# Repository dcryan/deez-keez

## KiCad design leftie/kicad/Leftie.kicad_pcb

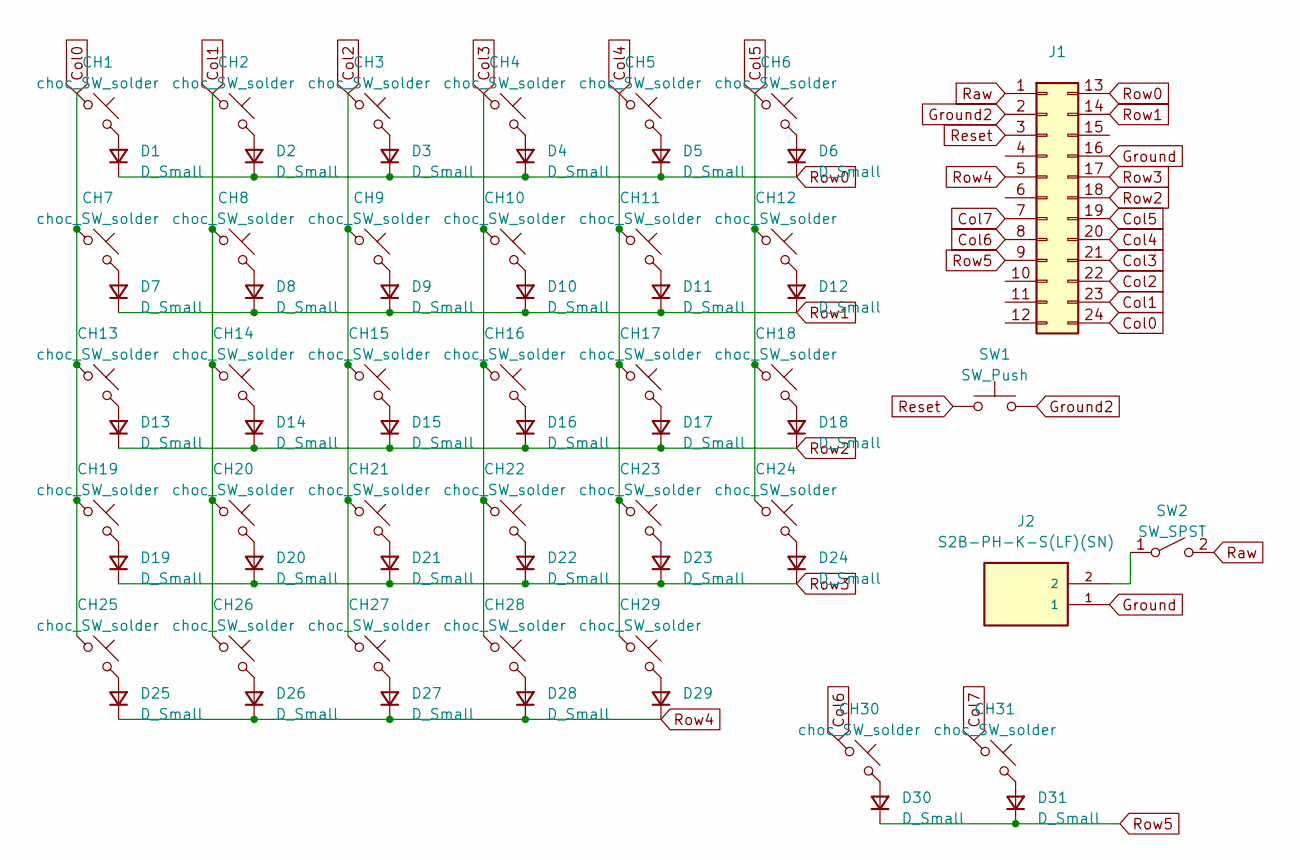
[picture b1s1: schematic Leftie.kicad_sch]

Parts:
CH1, CH2, CH3, CH4, CH5, CH6, CH7, CH8, CH9, CH10, CH11, CH12, CH13, CH14, CH15, CH16, CH17, CH18, CH19, CH20, CH21, CH22, CH23, CH24, CH25, CH26, CH27, CH28, CH29, CH30, CH31: choc_SW_solder; SW_choc_v1_1u
D1, D2, D3, D4, D5, D6, D7, D8, D9, D10, D11, D12, D13, D14, D15, D16, D17, D18, D19, D20, D21, D22, D23, D24, D25, D26, D27, D28, D29, D30, D31: D_Small; D_SOD-123
J1: Conn_02x12_Top_Bottom; ProMicro
J2: S2B-PH-K-S(LF)(SN); JST_S2B-PH-K-S(LF)(SN)
SW1: SW_Push; SW_SKHLLCA010
SW2: SW_SPST; SW_MSK12C02-HB

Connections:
Col0: CH1.1, CH7.1, CH13.1, CH19.1, CH25.1, J1.24
Col1: CH2.1, CH8.1, CH14.1, CH20.1, CH26.1, J1.23
Col2: CH3.1, CH9.1, CH15.1, CH21.1, CH27.1, J1.22
Col3: CH4.1, CH10.1, CH16.1, CH22.1, CH28.1, J1.21
Col4: CH5.1, CH11.1, CH17.1, CH23.1, CH29.1, J1.20
Col5: CH6.1, CH12.1, CH18.1, CH24.1, J1.19
Col6: CH30.1, J1.8
Col7: CH31.1, J1.7
Ground: J1.16, J2.1
Ground2: J1.2, SW1.2
unnamed: CH1.2, D1.2 (A)
unnamed: CH2.2, D2.2 (A)
unnamed: CH3.2, D3.2 (A)
unnamed: CH4.2, D4.2 (A)
unnamed: CH5.2, D5.2 (A)
unnamed: CH6.2, D6.2 (A)
unnamed: CH7.2, D7.2 (A)
unnamed: CH8.2, D8.2 (A)
unnamed: CH9.2, D9.2 (A)
unnamed: CH10.2, D10.2 (A)
unnamed: CH11.2, D11.2 (A)
unnamed: CH12.2, D12.2 (A)
unnamed: CH13.2, D13.2 (A)
unnamed: CH14.2, D14.2 (A)
unnamed: CH15.2, D15.2 (A)
unnamed: CH16.2, D16.2 (A)
unnamed: CH17.2, D17.2 (A)
unnamed: CH18.2, D18.2 (A)
unnamed: CH19.2, D19.2 (A)
unnamed: CH20.2, D20.2 (A)
unnamed: CH21.2, D21.2 (A)
unnamed: CH22.2, D22.2 (A)
unnamed: CH23.2, D23.2 (A)
unnamed: CH24.2, D24.2 (A)
unnamed: CH25.2, D25.2 (A)
unnamed: CH26.2, D26.2 (A)
unnamed: CH27.2, D27.2 (A)
unnamed: CH28.2, D28.2 (A)
unnamed: CH29.2, D29.2 (A)
unnamed: CH30.2, D30.2 (A)
unnamed: CH31.2, D31.2 (A)
unnamed: J2.2, SW2.1 (A)
Raw: J1.1, SW2.2 (B)
Reset: J1.3, SW1.1
Row0: D1.1 (K), D2.1 (K), D3.1 (K), D4.1 (K), D5.1 (K), D6.1 (K), J1.13
Row1: D7.1 (K), D8.1 (K), D9.1 (K), D10.1 (K), D11.1 (K), D12.1 (K), J1.14
Row2: D13.1 (K), D14.1 (K), D15.1 (K), D16.1 (K), D17.1 (K), D18.1 (K), J1.18
Row3: D19.1 (K), D20.1 (K), D21.1 (K), D22.1 (K), D23.1 (K), D24.1 (K), J1.17
Row4: D25.1 (K), D26.1 (K), D27.1 (K), D28.1 (K), D29.1 (K), J1.5
Row5: D30.1 (K), D31.1 (K), J1.9

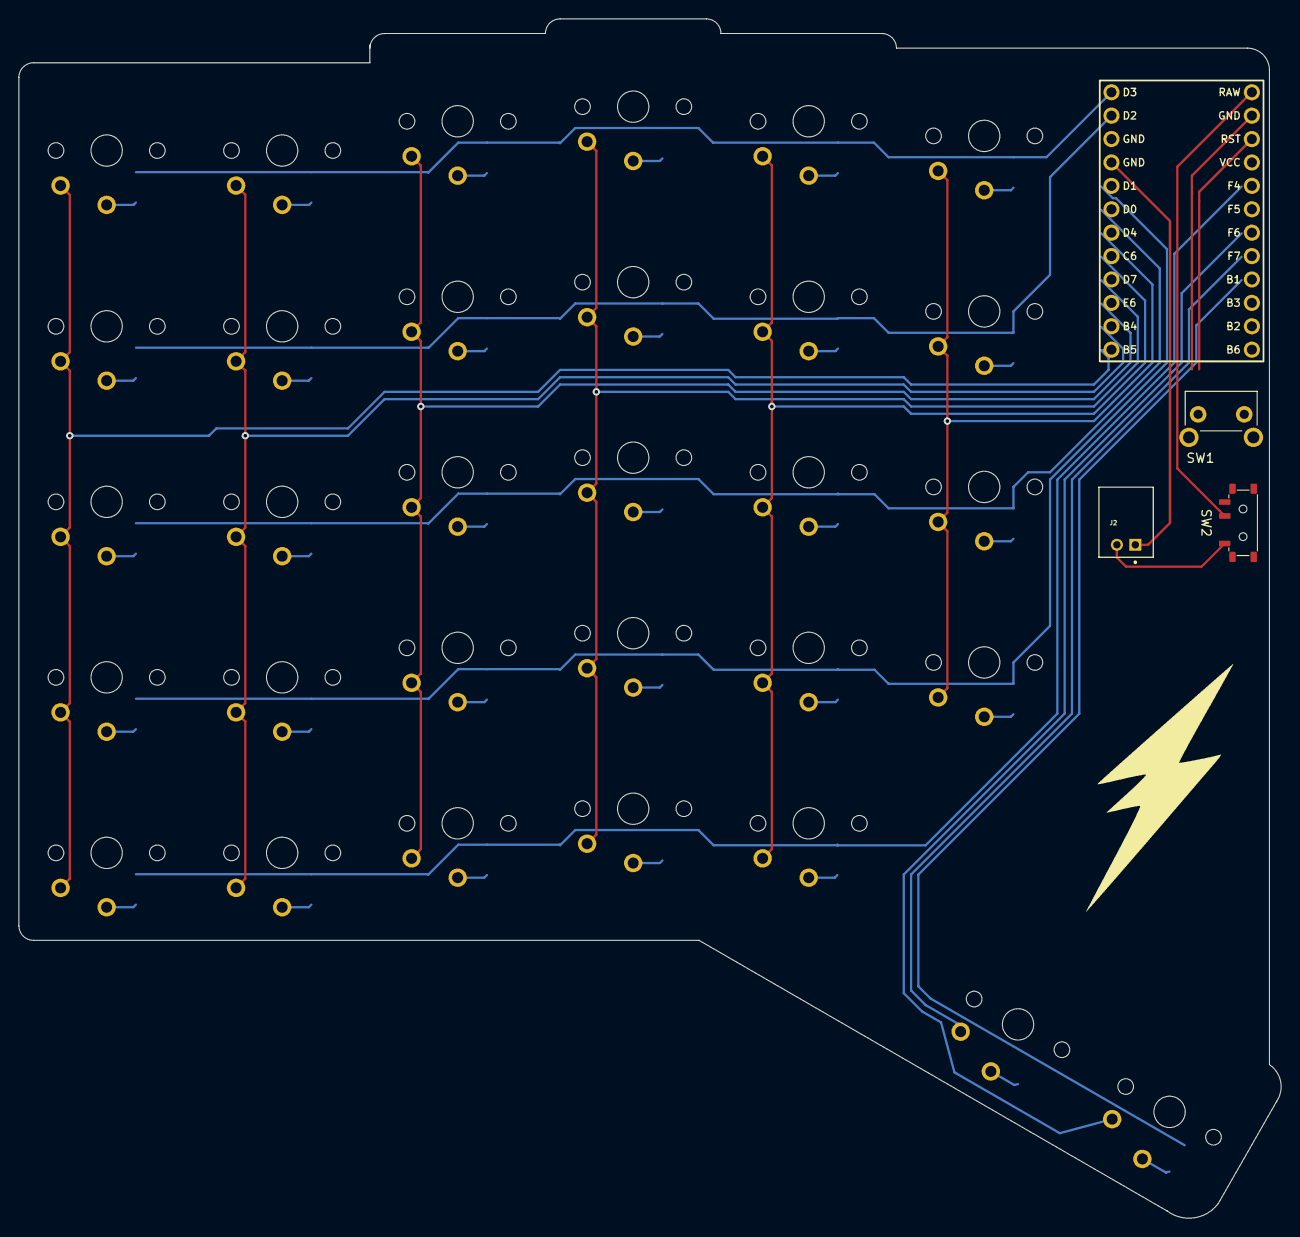
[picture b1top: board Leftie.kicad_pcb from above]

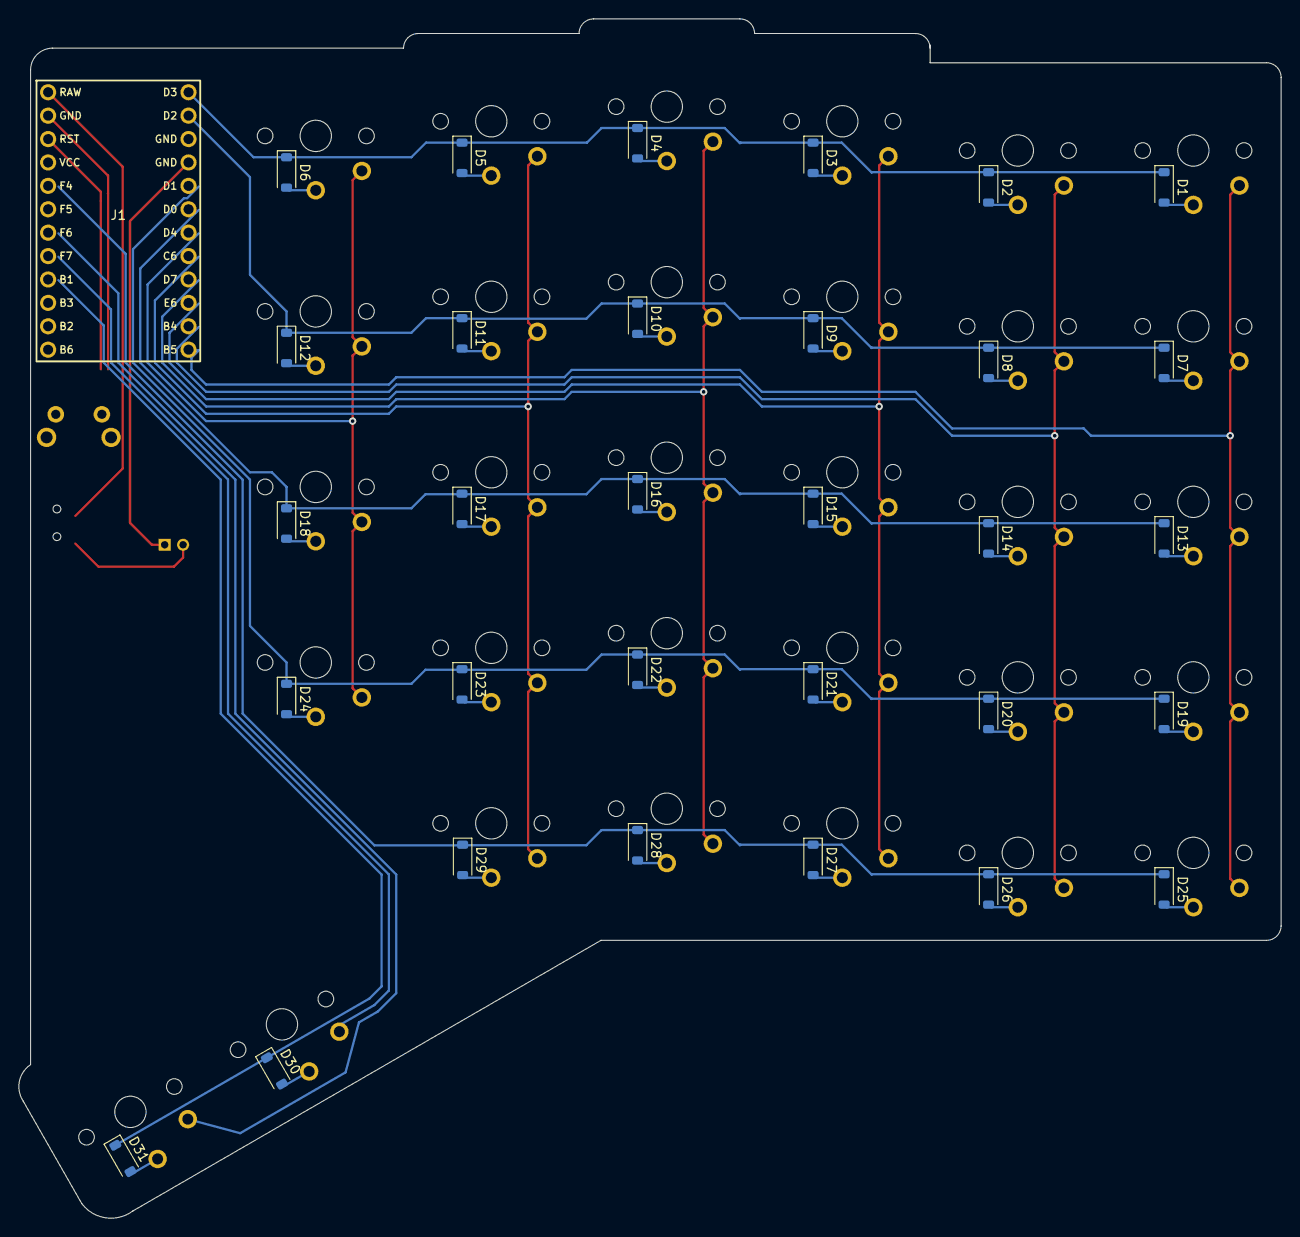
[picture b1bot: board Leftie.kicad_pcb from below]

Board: 2 copper layers, 137.0 x 130.2 mm, 66 parts (32 on the bottom side), 50 nets.

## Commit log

2023-08-01 feat: adding leftie keyboard
